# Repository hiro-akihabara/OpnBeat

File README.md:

# About the Project
OpnBeat is Arduino based open source Lo-fi sampler project.<br>
It's designed to be low cost, easy to understand, to use and to make.

<br>
3D rendered image by Blender

<br>
PCB

<br>
Demo video

# Why this project is beneficial

# Project Status
I have just developed its prototype (Ver.3), POC (Proof of concept), MVP (Minimum Viable Product) whatever it's called including hardware. But I need supports especially about improving its farmware because I'm mainly an electric engineer and not so good at programming.

# Links
* project on Hackaday.io<br>
[OpnBeat / DIY Lo-fi Sampler with ISD1700 series](https://hackaday.io/project/190273-opnbeat-diy-lo-fi-sampler-with-isd1700-serie

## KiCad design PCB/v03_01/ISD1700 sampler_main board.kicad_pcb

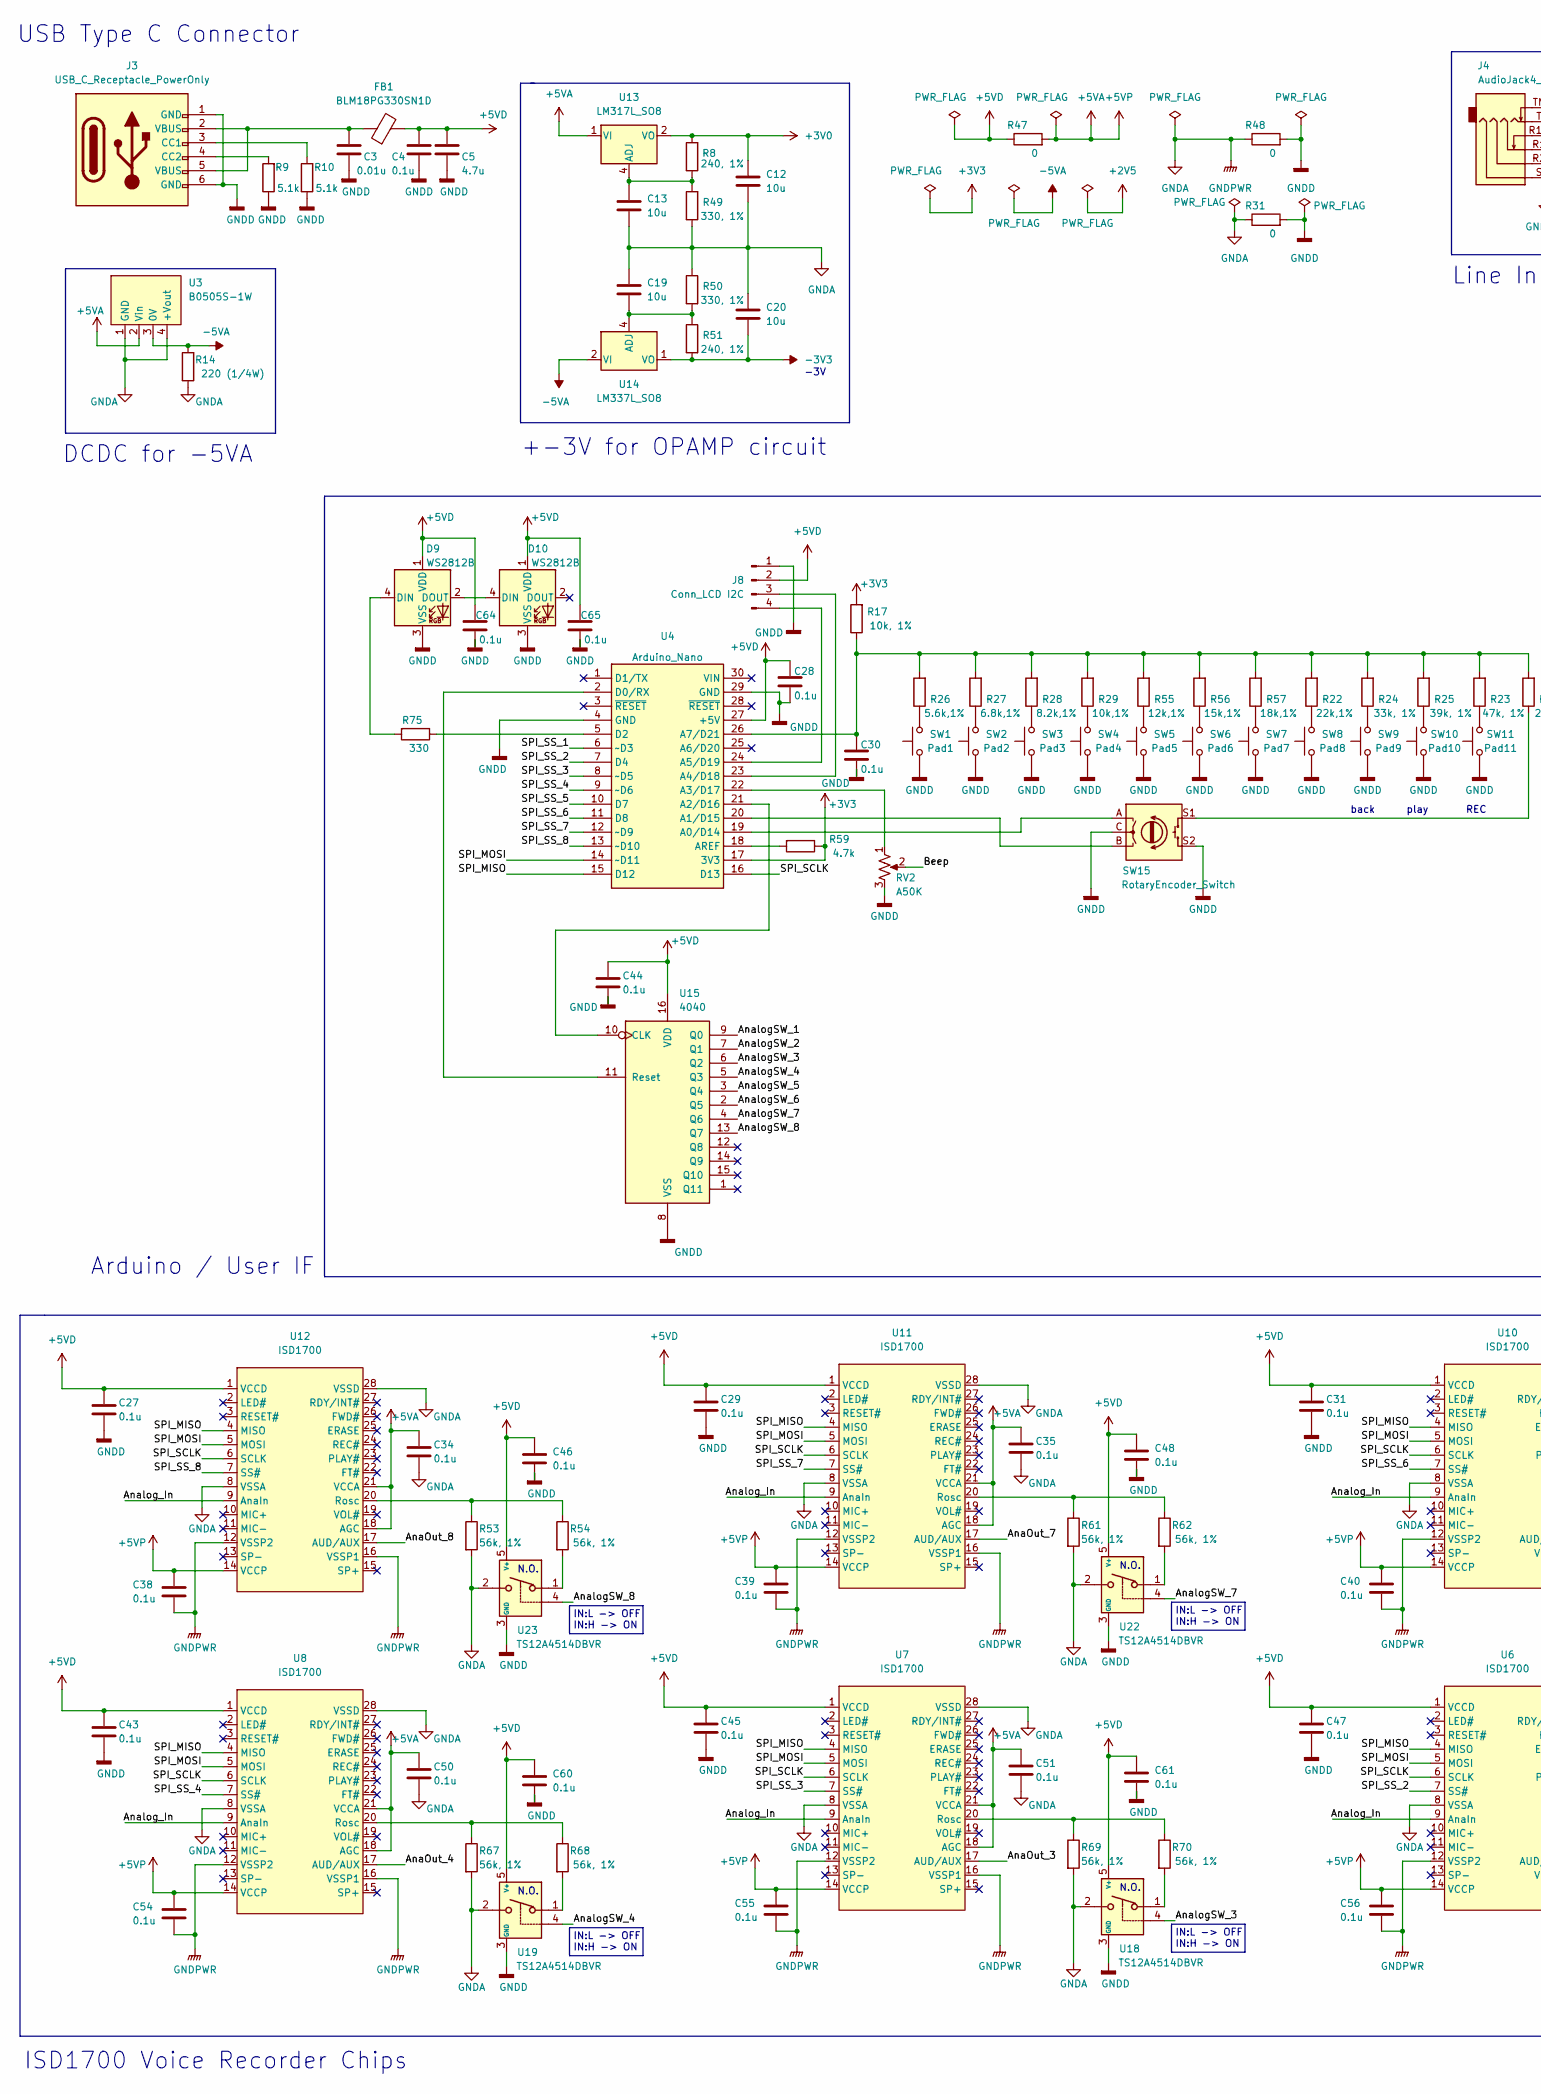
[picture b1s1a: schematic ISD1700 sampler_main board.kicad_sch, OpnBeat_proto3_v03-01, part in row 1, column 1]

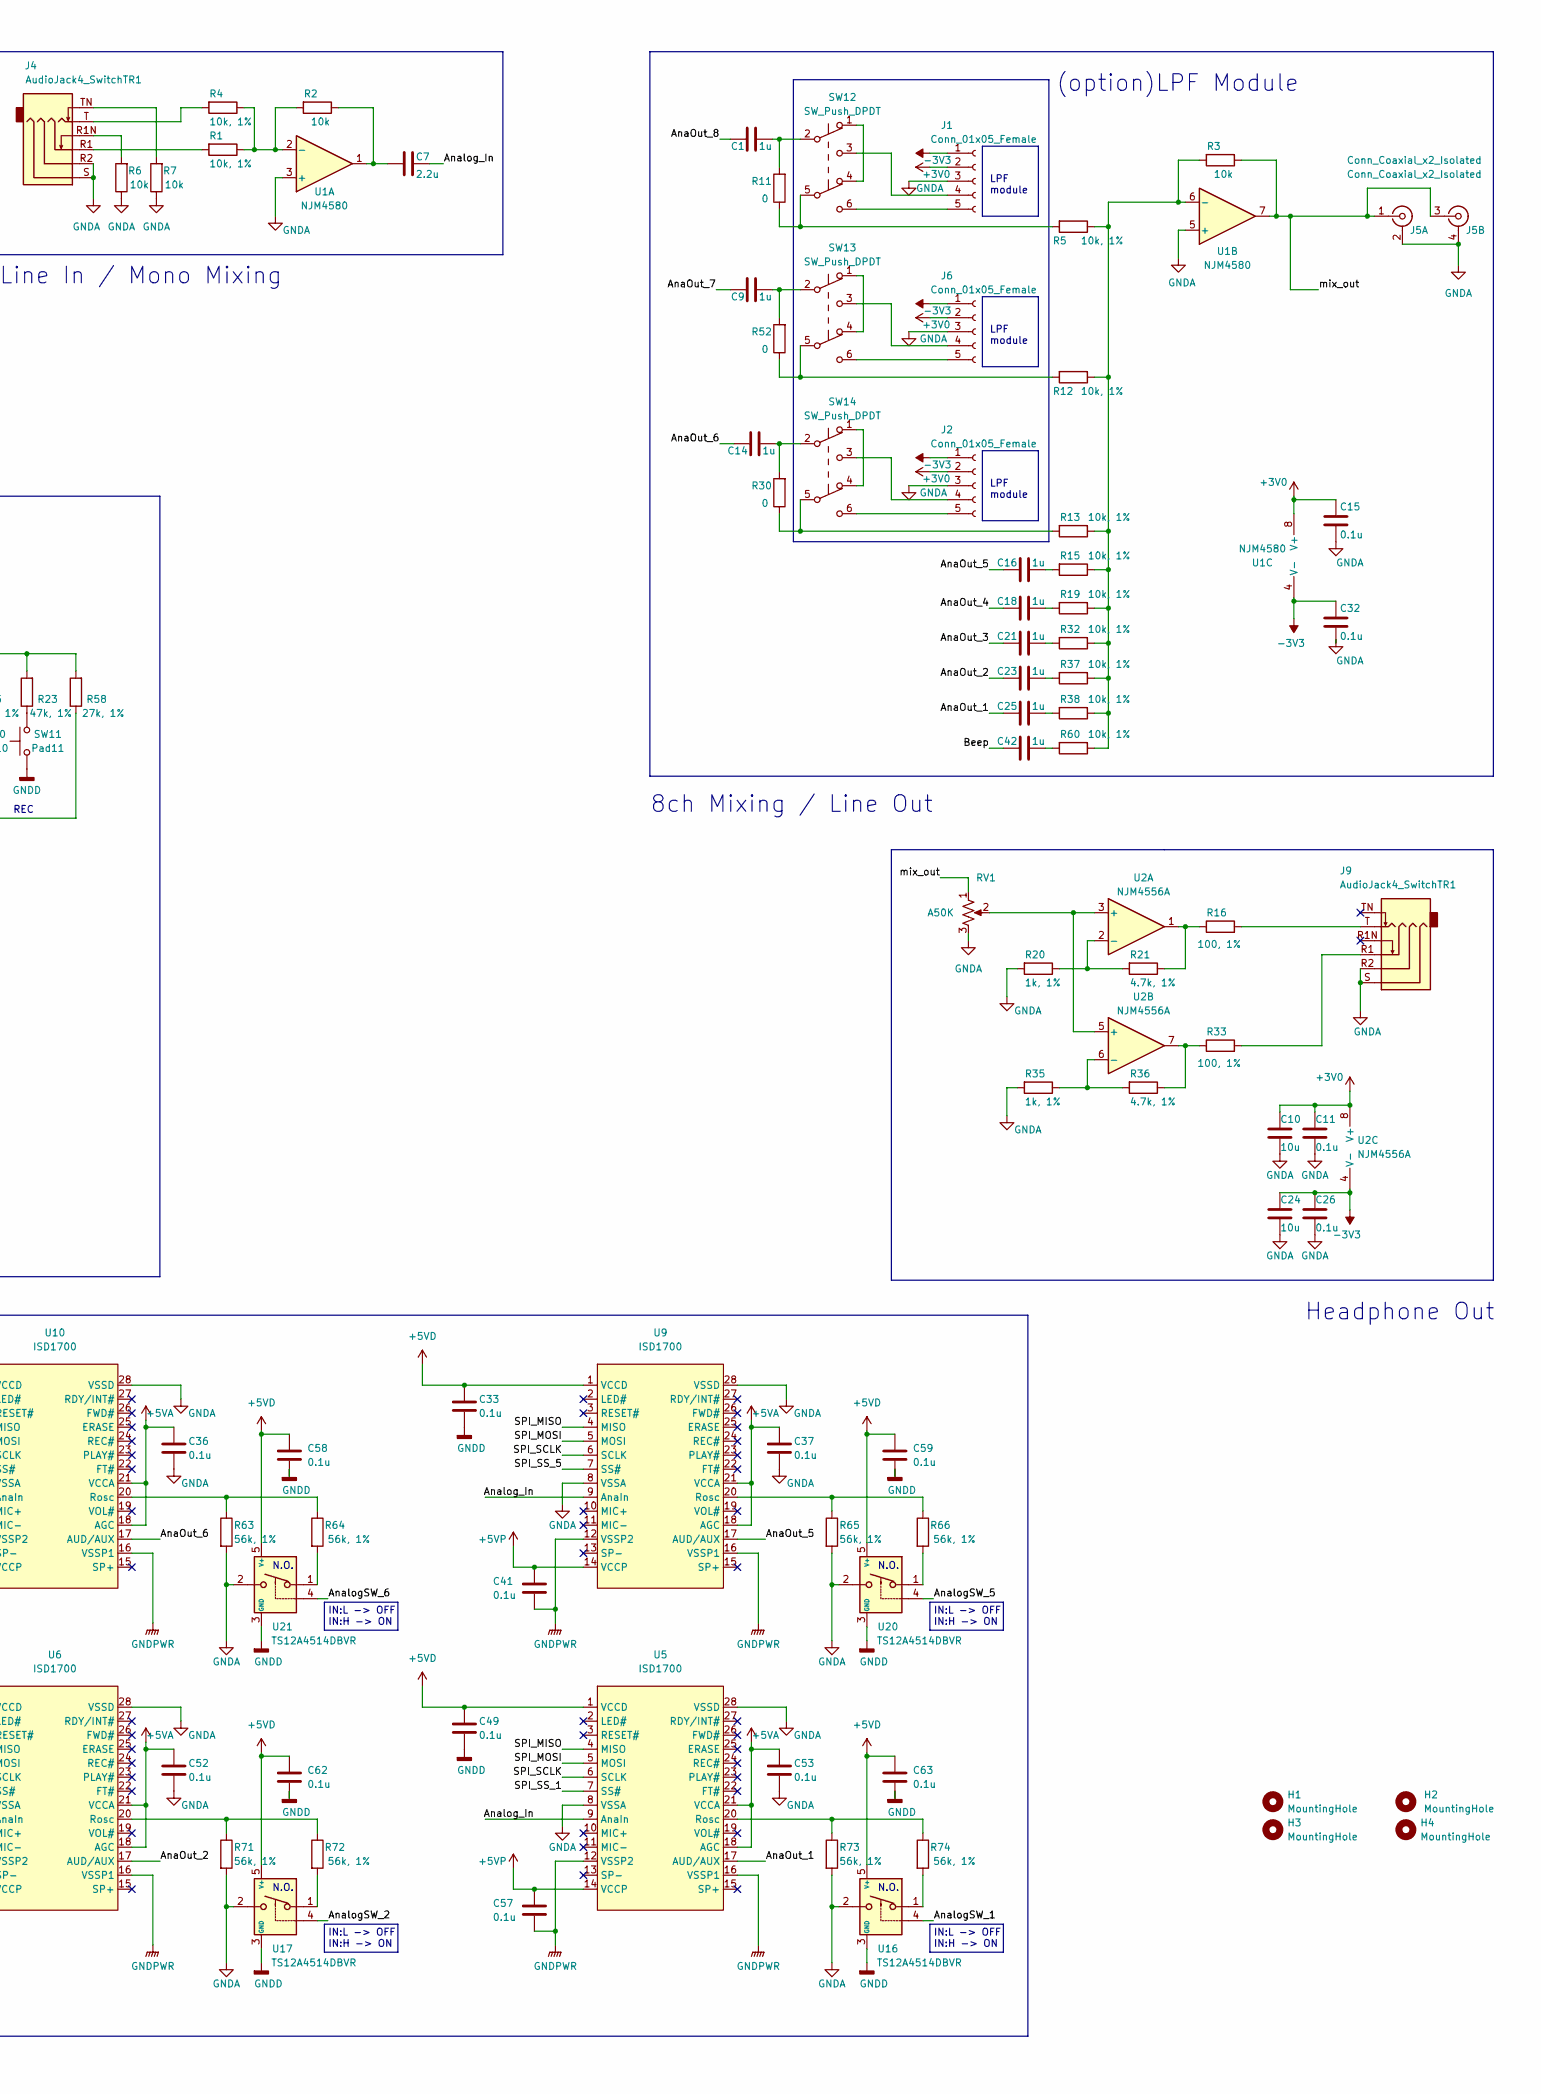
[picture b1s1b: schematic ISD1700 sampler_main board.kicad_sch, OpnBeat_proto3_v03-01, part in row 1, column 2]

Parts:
C1, C9, C14, C16, C18, C21, C23, C25, C42: 1u; C_0603_1608Metric
C3: 0.01u; C_0603_1608Metric
C4, C11, C15, C26, C27, C28, C29, C30, C31, C32, C33, C34, C35, C36, C37, C38, C39, C40, C41, C43, C44, C45, C46, C47, C48, C49, C50, C51, C52, C53, C54, C55, C56, C57, C58, C59, C60, C61, C62, C63, C64, C65: 0.1u; C_0603_1608Metric
C5: 4.7u; C_0603_1608Metric
C7: 2.2u; C_0603_1608Metric
C10, C12, C13, C19, C20, C24: 10u; C_0603_1608Metric
D9, D10: WS2812B; LED_WS2812B_PLCC4_5.0x5.0mm_P3.2mm
FB1: BLM18PG330SN1D; C_0603_1608Metric
H1, H2, H3, H4: MountingHole; MountingHole_3.2mm_M3
J1, J2, J6: Conn_01x05_Female; PinSocket_1x05_P2.54mm_Vertical
J3: USB_C_Receptacle_PowerOnly; USB C only Power
J4, J9: AudioJack4_SwitchTR1; Jack_3.5mm_PJ31060-I_Horizontal
J5: Conn_Coaxial_x2_Isolated; RCA-214
J8: Conn_LCD I2C; PinSocket_1x04_P2.54mm_Vertical
R1, R4, R5, R12, R13, R15, R17, R19, R32, R37, R38, R60: 10k, 1%; R_0603_1608Metric
R2, R3, R6, R7: 10k; R_0603_1608Metric
R8, R51: 240, 1%; R_0603_1608Metric
R9, R10: 5.1k; R_0603_1608Metric
R11, R30, R52: 0; R_0603_1608Metric
R14: 220 (1/4W); R_1206_3216Metric
R16, R33: 100, 1%; R_0603_1608Metric
R20, R35: 1k, 1%; R_0603_1608Metric
R21, R36: 4.7k, 1%; R_0603_1608Metric
R22: 22k,1%; R_0603_1608Metric
R23: 47k, 1%; R_0603_1608Metric
R24: 33k, 1%; R_0603_1608Metric
R25: 39k, 1%; R_0603_1608Metric
R26: 5.6k,1%; R_0603_1608Metric
R27: 6.8k,1%; R_0603_1608Metric
R28: 8.2k,1%; R_0603_1608Metric
R29: 10k,1%; R_0603_1608Metric
R31, R47, R48: 0; R_0805_2012Metric
R49, R50: 330, 1%; R_0603_1608Metric
R53, R54, R61, R62, R63, R64, R65, R66, R67, R68, R69, R70, R71, R72, R73, R74: 56k, 1%; R_0603_1608Metric
R55: 12k,1%; R_0603_1608Metric
R56: 15k,1%; R_0603_1608Metric
R57: 18k,1%; R_0603_1608Metric
R58: 27k, 1%; R_0603_1608Metric
R59: 4.7k; R_0603_1608Metric
R75: 330; R_0603_1608Metric
RV1, RV2: A50K; Potentiometer_Bourns_PTV09A-2_Single_Horizontal
SW1: Pad1; SW_Cherry_MX_PCB_1.00u
SW2: Pad2; SW_Cherry_MX_PCB_1.00u
SW3: Pad3; SW_Cherry_MX_PCB_1.00u
SW4: Pad4; SW_Cherry_MX_PCB_1.00u
SW5: Pad5; SW_Cherry_MX_PCB_1.00u
SW6: Pad6; SW_Cherry_MX_PCB_1.00u
SW7: Pad7; SW_Cherry_MX_PCB_1.00u
SW8: Pad8; SW_Cherry_MX_PCB_1.00u
SW9: Pad9; SW_Cherry_MX_PCB_1.00u
SW10: Pad10; SW_Cherry_MX_PCB_1.00u
SW11: Pad11; SW_Cherry_MX_PCB_1.00u
SW12, SW13, SW14: SW_Push_DPDT; Push SW DPDT
SW15: RotaryEncoder_Switch; RotaryEncoder_Alps_EC11E-Switch_Vertical_H20mm_CircularMoun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
U1: NJM4580; TSSOP-8_4.4x3mm_P0.65mm
U2: NJM4556A; TSSOP-8_4.4x3mm_P0.65mm
U3: B0505S-1W
U4: Arduino_Nano
U5, U6, U7, U8, U9, U10, U11, U12: ISD1700; SOIC-28W_7.5x17.9mm_P1.27mm
U13: LM317L_SO8; SOIC-8_3.9x4.9mm_P1.27mm
U14: LM337L_SO8; SOIC-8_3.9x4.9mm_P1.27mm
U15: 4040; SOIC-16_3.9x9.9mm_P1.27mm
U16, U17, U18, U19, U20, U21, U22, U23: TS12A4514DBVR; SOT-23-5

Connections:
+3V0: C10.1, C11.1, C12.1, C15.1, J1.2, J2.2, J6.2, R8.2, U1.8 (V+), U2.8 (V+), U13.2 (VO), U13.3 (VO), U13.6 (VO), U13.7 (VO)
+3V3: R17.2, R59.1, U4.17 (3V3)
+5VA: C34.1, C35.1, C36.1, C37.1, C38.1, C39.1, C40.1, C41.1, C50.1, C51.1, C52.1, C53.1, C54.1, C55.1, C56.1, C57.1, R47.2, U3.2 (Vin), U5.14 (VCCP), U5.18 (AGC), U5.21 (VCCA), U6.14 (VCCP), U6.18 (AGC), U6.21 (VCCA), U7.14 (VCCP), U7.18 (AGC), U7.21 (VCCA), U8.14 (VCCP), U8.18 (AGC), U8.21 (VCCA), U9.14 (VCCP), U9.18 (AGC), U9.21 (VCCA), U10.14 (VCCP), U10.18 (AGC), U10.21 (VCCA), U11.14 (VCCP), U11.18 (AGC), U11.21 (VCCA), U12.14 (VCCP), U12.18 (AGC), U12.21 (VCCA), U13.1 (VI)
+5VD: C4.1, C5.1, C27.1, C28.1, C29.1, C31.1, C33.1, C43.1, C44.1, C45.1, C46.1, C47.1, C48.1, C49.1, C58.1, C59.1, C60.1, C61.1, C62.1, C63.1, C64.1, C65.1, D9.1 (VDD), D10.1 (VDD), FB1.2, J8.2, R47.1, U4.27 (+5V), U5.1 (VCCD), U6.1 (VCCD), U7.1 (VCCD), U8.1 (VCCD), U9.1 (VCCD), U10.1 (VCCD), U11.1 (VCCD), U12.1 (VCCD), U15.16 (VDD), U16.5 (V+), U17.5 (V+), U18.5 (V+), U19.5 (V+), U20.5 (V+), U21.5 (V+), U22.5 (V+), U23.5 (V+)
-3V3: C20.1, C24.1, C26.1, C32.1, J1.1, J2.1, J6.1, R51.2, U1.4 (V-), U2.4 (V-), U14.1 (VO)
-5VA: R14.2, U3.3 (0V), U14.2 (VI), U14.3 (VI), U14.6 (VI), U14.7 (VI)
/AnaOut_1: C25.2, U5.17 (AUD/AUX)
/AnaOut_2: C23.2, U6.17 (AUD/AUX)
/AnaOut_3: C21.2, U7.17 (AUD/AUX)
/AnaOut_4: C18.2, U8.17 (AUD/AUX)
/AnaOut_5: C16.2, U9.17 (AUD/AUX)
/AnaOut_6: C14.2, U10.17 (AUD/AUX)
/AnaOut_7: C9.2, U11.17 (AUD/AUX)
/AnaOut_8: C1.2, U12.17 (AUD/AUX)
/AnalogSW_1: U15.9 (Q0), U16.4
/AnalogSW_2: U15.7 (Q1), U17.4
/AnalogSW_3: U15.6 (Q2), U18.4
/AnalogSW_4: U15.5 (Q3), U19.4
/AnalogSW_5: U15.3 (Q4), U20.4
/AnalogSW_6: U15.2 (Q5), U21.4
/AnalogSW_7: U15.4 (Q6), U22.4
/AnalogSW_8: U15.13 (Q7), U23.4
/Analog_In: C7.1, U5.9 (AnaIn), U6.9 (AnaIn), U7.9 (AnaIn), U8.9 (AnaIn), U9.9 (AnaIn), U10.9 (AnaIn), U11.9 (AnaIn), U12.9 (AnaIn)
/Beep: C42.2, RV2.2
/SPI_MISO: U4.15 (D12), U5.4 (MISO), U6.4 (MISO), U7.4 (MISO), U8.4 (MISO), U9.4 (MISO), U10.4 (MISO), U11.4 (MISO), U12.4 (MISO)
/SPI_MOSI: U4.14 (~D11), U5.5 (MOSI), U6.5 (MOSI), U7.5 (MOSI), U8.5 (MOSI), U9.5 (MOSI), U10.5 (MOSI), U11.5 (MOSI), U12.5 (MOSI)
/SPI_SCLK: U4.16 (D13), U5.6 (SCLK), U6.6 (SCLK), U7.6 (SCLK), U8.6 (SCLK), U9.6 (SCLK), U10.6 (SCLK), U11.6 (SCLK), U12.6 (SCLK)
/SPI_SS_1: U4.6 (~D3), U5.7 (SS#)
/SPI_SS_2: U4.7 (D4), U6.7 (SS#)
/SPI_SS_3: U4.8 (~D5), U7.7 (SS#)
/SPI_SS_4: U4.9 (~D6), U8.7 (SS#)
/SPI_SS_5: U4.10 (D7), U9.7 (SS#)
/SPI_SS_6: U4.11 (D8), U10.7 (SS#)
/SPI_SS_7: U4.12 (~D9), U11.7 (SS#)
/SPI_SS_8: U4.13 (~D10), U12.7 (SS#)
/mix_out: J5.1 (In1), J5.3 (In2), R3.1, RV1.1, U1.7
GNDA: C10.2, C11.2, C12.2, C13.2, C15.2, C19.2, C20.2, C24.2, C26.2, C32.2, C34.2, C35.2, C36.2, C37.2, C38.2, C39.2, C40.2, C41.2, C50.2, C51.2, C52.2, C53.2, C54.2, C55.2, C56.2, C57.2, J1.3, J2.3, J4.R2, J4.S, J5.2 (Ext1), J5.4 (Ext2), J6.3, J9.R2, J9.S, R6.1, R7.1, R14.1, R20.2, R31.1, R35.2, R48.1, R49.1, R50.1, R53.2, R61.2, R63.2, R65.2, R67.2, R69.2, R71.2, R73.2, RV1.3, U1.3 (+), U1.5 (+), U3.1 (GND), U3.4 (+Vout), U5.8 (VSSA), U5.12 (VSSP2), U5.16 (VSSP1), U5.28 (VSSD), U6.8 (VSSA), U6.12 (VSSP2), U6.16 (VSSP1), U6.28 (VSSD), U7.8 (VSSA), U7.12 (VSSP2), U7.16 (VSSP1), U7.28 (VSSD), U8.8 (VSSA), U8.12 (VSSP2), U8.16 (VSSP1), U8.28 (VSSD), U9.8 (VSSA), U9.12 (VSSP2), U9.16 (VSSP1), U9.28 (VSSD), U10.8 (VSSA), U10.12 (VSSP2), U10.16 (VSSP1), U10.28 (VSSD), U11.8 (VSSA), U11.12 (VSSP2), U11.16 (VSSP1), U11.28 (VSSD), U12.8 (VSSA), U12.12 (VSSP2), U12.16 (VSSP1), U12.28 (VSSD), U16.2, U17.2, U18.2, U19.2, U20.2, U21.2, U22.2, U23.2
GNDD: C3.2, C4.2, C5.2, C27.2, C28.2, C29.2, C30.2, C31.2, C33.2, C43.2, C44.2, C45.2, C46.2, C47.2, C48.2, C49.2, C58.2, C59.2, C60.2, C61.2, C62.2, C63.2, C64.2, C65.2, D9.3 (VSS), D10.3 (VSS), J3.1 (GND), J3.6 (GND), J8.1, R9.1, R10.1, R31.2, R48.2, RV2.3, SW1.1, SW2.1, SW3.1, SW4.1, SW5.1, SW6.1, SW7.1, SW8.1, SW9.1, SW10.1, SW11.1, SW15.C, SW15.S2, U4.4 (GND), U4.29 (GND), U15.8 (VSS), U16.3 (GND), U17.3 (GND), U18.3 (GND), U19.3 (GND), U20.3 (GND), U21.3 (GND), U22.3 (GND), U23.3 (GND)
unnamed: C1.1, R11.2, SW12.2 (B)
unnamed: C3.1, FB1.1, J3.2 (VBUS), J3.5 (VBUS)
unnamed: C7.2, R2.1, U1.1
unnamed: C9.1, R52.2, SW13.2 (B)
unnamed: C13.1, R8.1, R49.2, U13.4 (ADJ)
unnamed: C14.1, R30.2, SW14.2 (B)
unnamed: C16.1, R15.2
unnamed: C18.1, R19.2
unnamed: C19.1, R50.2, R51.1, U14.4 (ADJ)
unnamed: C21.1, R32.2
unnamed: C23.1, R37.2
unnamed: C25.1, R38.2
unnamed: C30.1, R17.1, R22.2, R23.2, R24.2, R25.2, R26.2, R27.2, R28.2, R29.2, R55.2, R56.2, R57.2, R58.2, U4.26 (A7/D21)
unnamed: C42.1, R60.2
unnamed: D9.4 (DIN), R75.2
unnamed: D9.2 (DOUT), D10.4 (DIN)
unnamed: J1.4, SW12.3 (C)
unnamed: J1.5, SW12.6 (C)
unnamed: J2.4, SW14.3 (C)
unnamed: J2.5, SW14.6 (C)
unnamed: J3.3 (CC1), R10.2
unnamed: J3.4 (CC2), R9.2
unnamed: J4.R1, R1.2
unnamed: J4.R1N, R6.2
unnamed: J4.T, R4.2
unnamed: J4.TN, R7.2
unnamed: J6.4, SW13.3 (C)
unnamed: J6.5, SW13.6 (C)
unnamed: J8.3, U4.23 (A4/D18)
unnamed: J8.4, U4.24 (A5/D19)
unnamed: J9.R1, R33.2
unnamed: J9.T, R16.2
unnamed: R1.1, R2.2, R4.1, U1.2 (-)
unnamed: R5.2, R11.1, SW12.5 (B)
unnamed: R3.2, R5.1, R12.1, R13.1, R15.1, R19.1, R32.1, R37.1, R38.1, R60.1, U1.6 (-)
unnamed: R12.2, R52.1, SW13.5 (B)
unnamed: R13.2, R30.1, SW14.5 (B)
unnamed: R16.1, R21.1, U2.1
unnamed: R20.1, R21.2, U2.2 (-)
unnamed: R22.1, SW8.2
unnamed: R23.1, SW11.2
unnamed: R24.1, SW9.2
unnamed: R25.1, SW10.2
unnamed: R26.1, SW1.2
unnamed: R27.1, SW2.2
unnamed: R28.1, SW3.2
unnamed: R29.1, SW4.2
unnamed: R33.1, R36.1, U2.7
unnamed: R35.1, R36.2, U2.6 (-)
unnamed: R53.1, R54.1, U12.20 (Rosc)
unnamed: R54.2, U23.1
unnamed: R55.1, SW5.2
unnamed: R56.1, SW6.2
unnamed: R57.1, SW7.2
unnamed: R58.1, SW15.S1
unnamed: R59.2, U4.18 (AREF)
unnamed: R61.1, R62.1, U11.20 (Rosc)
unnamed: R62.2, U22.1
unnamed: R63.1, R64.1, U10.20 (Rosc)
unnamed: R64.2, U21.1
unnamed: R65.1, R66.1, U9.20 (Rosc)
unnamed: R66.2, U20.1
unnamed: R67.1, R68.1, U8.20 (Rosc)
unnamed: R68.2, U19.1
unnamed: R69.1, R70.1, U7.20 (Rosc)
unnamed: R70.2, U18.1
unnamed: R71.1, R72.1, U6.20 (Rosc)
unnamed: R72.2, U17.1
unnamed: R73.1, R74.1, U5.20 (Rosc)
unnamed: R74.2, U16.1
unnamed: R75.1, U4.5 (D2)
unnamed: RV1.2, U2.3 (+), U2.5 (+)
unnamed: RV2.1, U4.22 (A3/D17)
unnamed: SW12.1 (A), SW12.4 (A)
unnamed: SW13.1 (A), SW13.4 (A)
unnamed: SW14.1 (A), SW14.4 (A)
unnamed: SW15.A, U4.19 (A0/D14)
unnamed: SW15.B, U4.20 (A1/D15)
unnamed: U4.21 (A2/D16), U15.10 (CLK)
unnamed: U4.2 (D0/RX), U15.11 (Reset)

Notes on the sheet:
Headphone Out
IN:L -> OFF IN:H -> ON
N.O.
(option)LPF Module
DCDC for -5VA
Line In / Mono Mixing
+-3V for OPAMP circuit
LPF module
ISD1700 Voice Recorder Chips
8ch Mixing / Line Out
play
back
REC
USB Type C Connector
Arduino / User IF
-3V

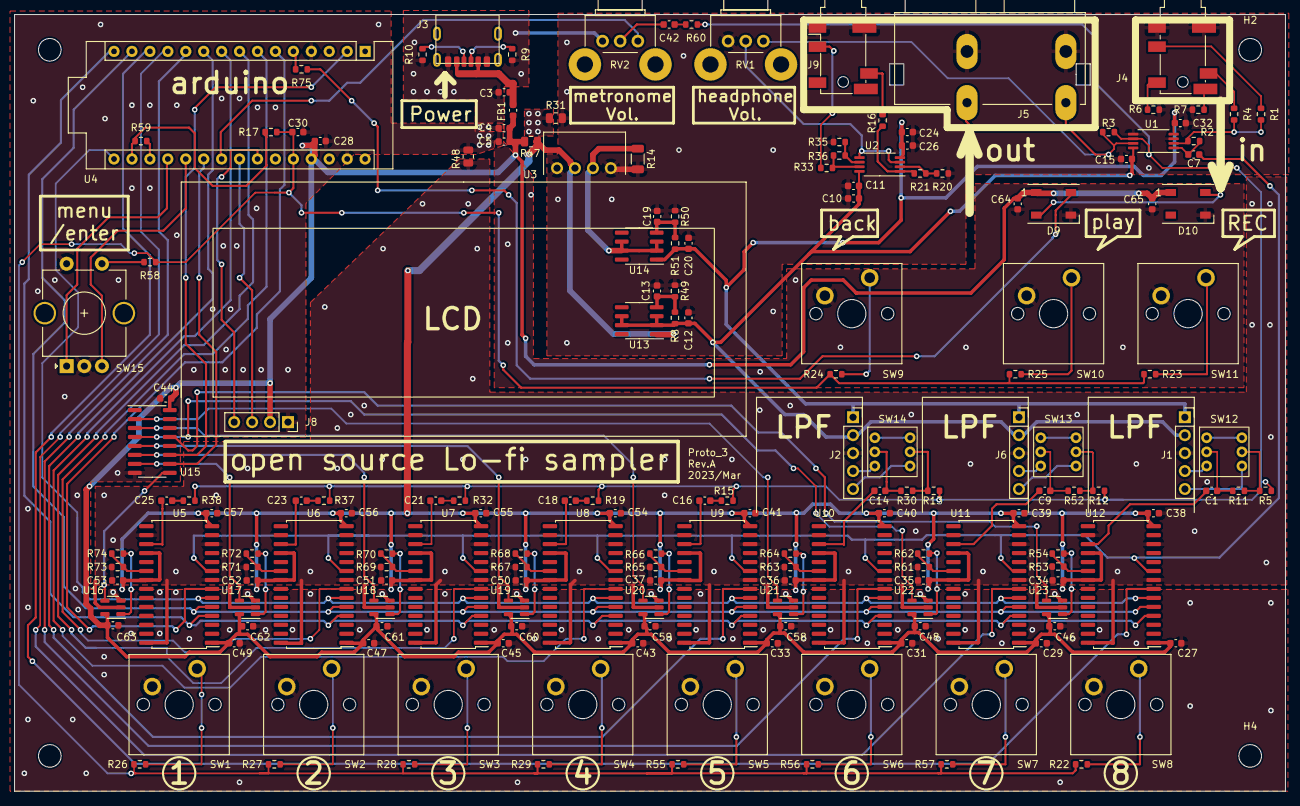
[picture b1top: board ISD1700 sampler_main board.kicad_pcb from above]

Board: 2 copper layers, 180.0 x 110.0 mm, 180 parts (0 on the bottom side), 118 nets.

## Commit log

2023-04-03 Create images
2023-04-04 Create LICENSE
2023-04-04 Create test
